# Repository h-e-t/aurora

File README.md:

# Aurora

## Migration plan

Do not rewrite the entire application in one pass. Use this order:

1. Install and pin an ESP-IDF version.
2. Create an empty native ESP-IDF project.
3. Make `app_main()` build, flash, and print a log message.
4. Add GPIO and LED control.
5. Add I2C and validate the MPU6050 independently.
6. Add SPI and validate the BMP280 independently.
7. Add LEDC and validate each servo with the motor/fin mechanism disconnected.
8. Add UART and validate GPS parsing.
9. Port the navigation math without hardware dependencies.
10. Add sensor-to-navigation queues.
11. Add the flight-control task.
12. Add actuator arming and safety interlocks.
13. Add telemetry and fault handling.
14. Only then test the complete system.

## Native Ubuntu build

This project is built for the ESP32-S2 with ESP-IDF v6.0.2. 

For a new Ubuntu machine, install ESP-IDF using [Espressif's Linux setup instructions](https://docs.espressif.com/projects/esp-idf/en/v6.0.2/esp32s2/get-started/linux-macos-start-project.html). The ESP-IDF checkout used on this machine is `../esp/esp-idf-v6.0.2`, installed with the `esp32s2` target.

From the Aurora repository root, activate that installation and build:

```bash
source ../esp/esp-idf-v6.0.2/export.sh
idf.py set-target esp32s2  # first build only, or when changing targets
idf.py build
```

The firmware image is written to `build/mekf_firmware.bin`. To flash a connected board, run `idf.py flash`; to open its serial monitor, run `idf.py monitor`.

## Hardware documentation

See [docs/components/README.md](docs/components/README.md) for official component references and a script to download the vendor PDFs.

## Format C/C++ files on commit

The repository hook formats staged C/C++ files with `.clang-format` while preserving unstaged edits. Enable it once in this clone:

```bash
git config --local core.hooksPath .githooks
```

The hook requires Python 3 and `clang-format` on `PATH`.

## ESP32 application task affinity

Keep application work on separate cores: reserve core 0 for time-critical IMU
sampling and state propagation, and pin GPS, barometer, SD-card, and logging
tasks to core 1. Keep blocking I/O and log output off the propagation core.

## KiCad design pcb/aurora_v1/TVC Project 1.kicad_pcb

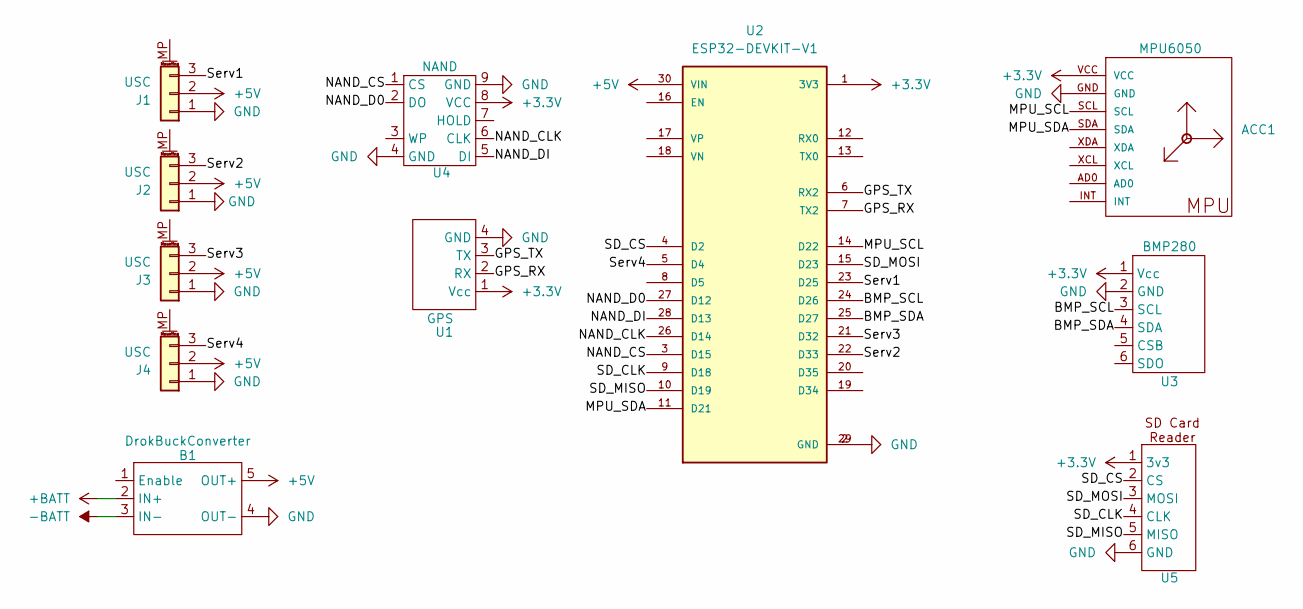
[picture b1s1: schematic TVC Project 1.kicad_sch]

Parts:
ACC1: MPU6050; GY-521
B1: DrokBuckConverter; HT_BuckConverter
J1, J2, J3, J4: USC; PinHeader_1x03_P2.54mm_Vertical
U1: GPS; HT_GY-GPS6MV2
U2: ESP32-DEVKIT-V1; MODULE_ESP32_DEVKIT_V1; PARTREV N/A
U3: BMP280; HT_BMP280
U4: NAND; SON127P600X800X80-9N
U5: HT_SDCardReader

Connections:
+3.3V: ACC1.VCC, U1.1 (Vcc), U2.1 (3V3), U3.1 (Vcc), U4.8 (VCC), U5.1 (3v3)
+5V: B1.5 (OUT+), J1.2 (VCC), J2.2 (VCC), J3.2 (VCC), J4.2 (VCC), U2.30 (VIN)
+BATT: B1.2 (IN+)
-BATT: B1.3 (IN-)
/BMP_SCL: U2.24 (D26), U3.3 (SCL)
/BMP_SDA: U2.25 (D27), U3.4 (SDA)
/GPS_RX: U1.2 (RX), U2.7 (TX2)
/GPS_TX: U1.3 (TX), U2.6 (RX2)
/MPU_SCL: ACC1.SCL, U2.14 (D22)
/MPU_SDA: ACC1.SDA, U2.11 (D21)
/NAND_CLK: U2.26 (D14), U4.6 (CLK)
/NAND_CS: U2.3 (D15), U4.1 (CS)
/NAND_D0: U2.27 (D12), U4.2 (DO)
/NAND_DI: U2.28 (D13), U4.5 (DI)
/SD_CLK: U2.9 (D18), U5.4 (CLK)
/SD_CS: U2.4 (D2), U5.2 (CS)
/SD_MISO: U2.10 (D19), U5.5 (MISO)
/SD_MOSI: U2.15 (D23), U5.3 (MOSI)
/Serv1: J1.3 (Signal), U2.23 (D25)
/Serv2: J2.3 (Signal), U2.22 (D33)
/Serv3: J3.3 (Signal), U2.21 (D32)
/Serv4: J4.3 (Signal), U2.5 (D4)
GND: ACC1.GND, B1.4 (OUT-), J1.1 (GND), J2.1 (GND), J3.1 (GND), J4.1 (GND), U1.4 (GND), U2.2 (GND), U2.29 (GND), U3.2 (GND), U4.4 (GND), U4.9 (GND), U5.6 (GND)

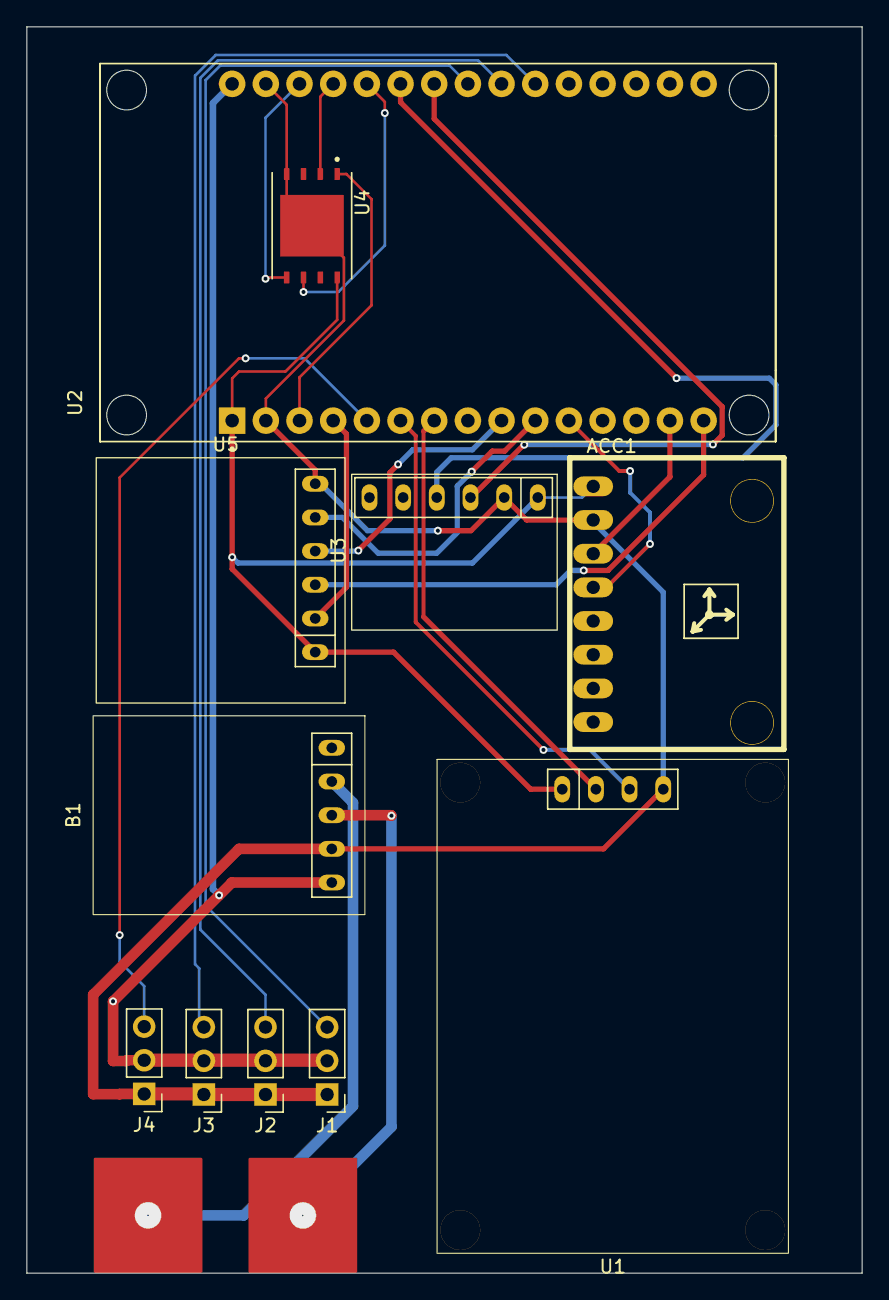
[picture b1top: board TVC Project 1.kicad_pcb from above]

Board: 2 copper layers, 63.0 x 94.0 mm, 11 parts (0 on the bottom side), 21 nets.
